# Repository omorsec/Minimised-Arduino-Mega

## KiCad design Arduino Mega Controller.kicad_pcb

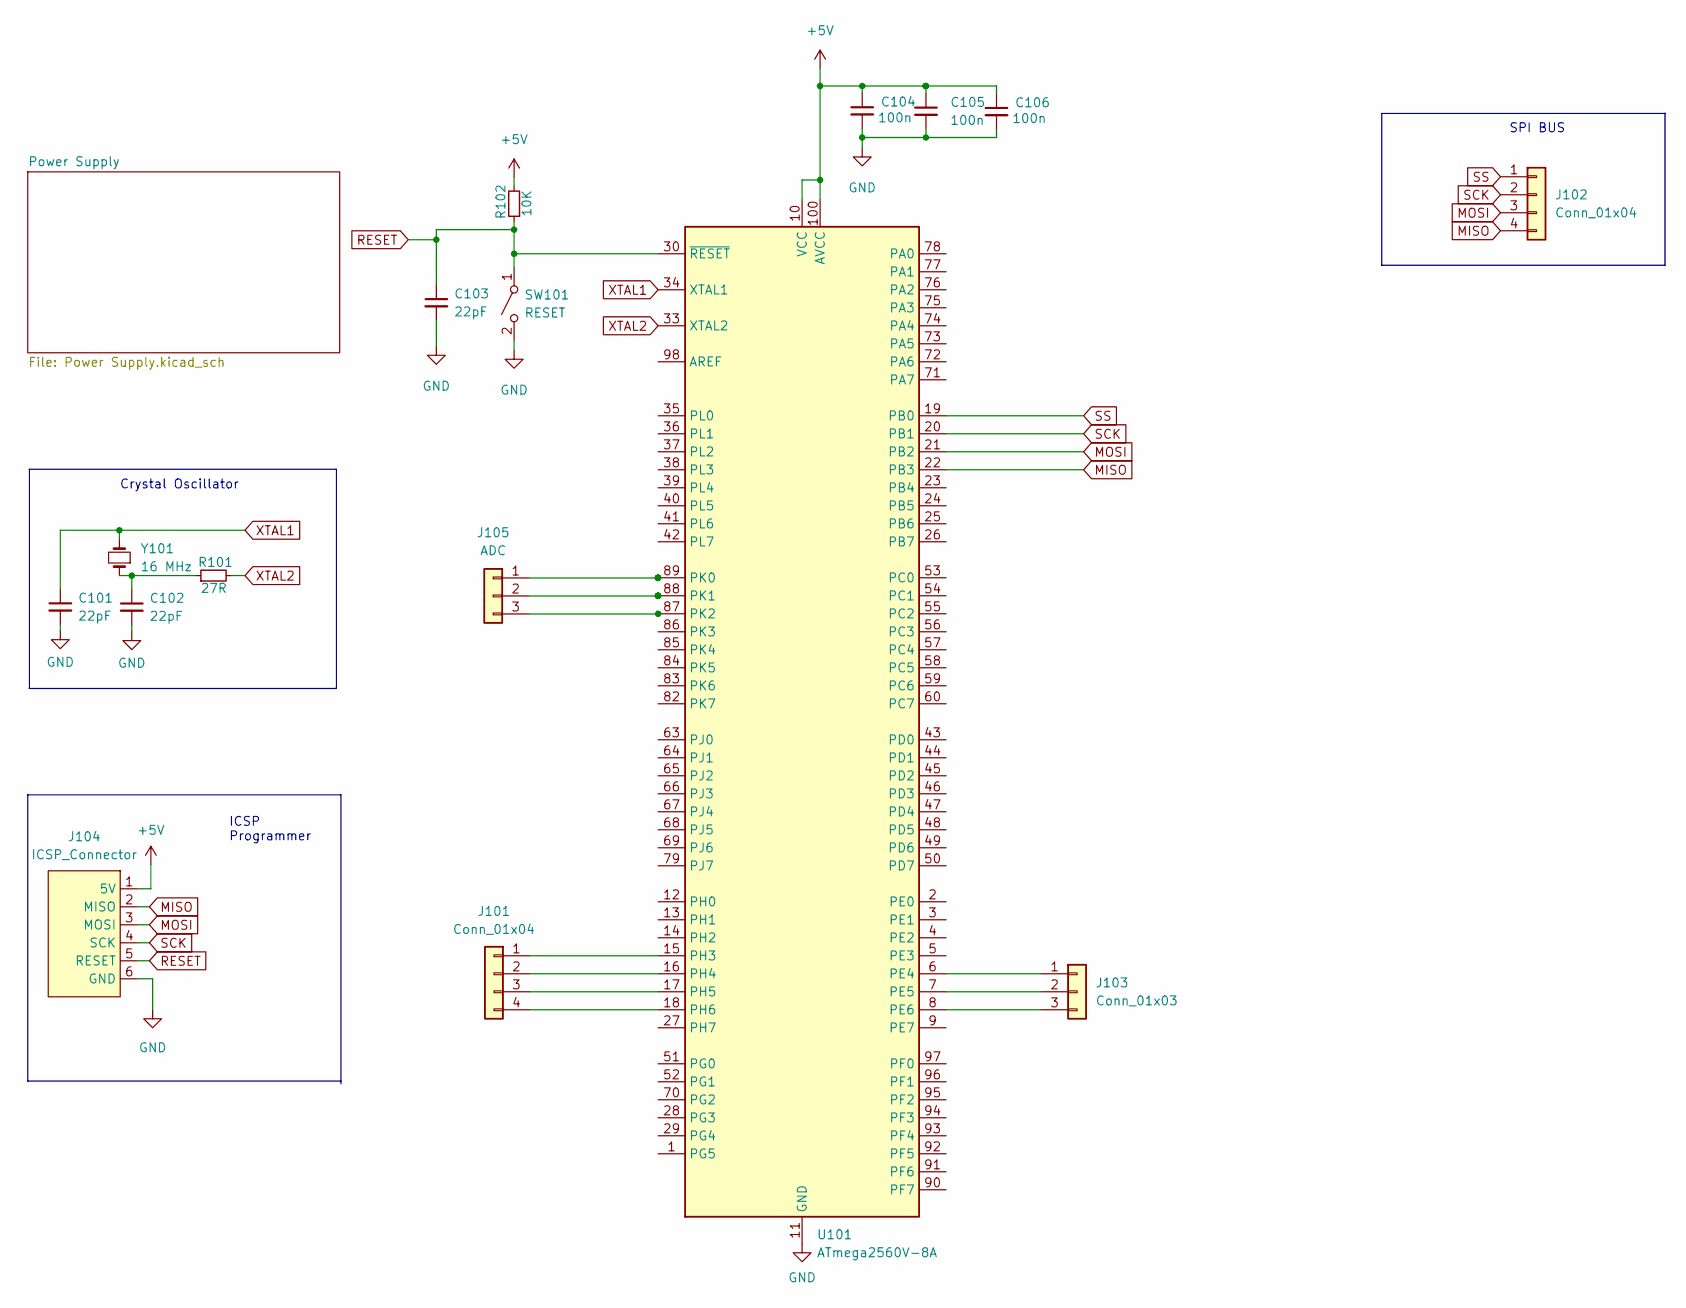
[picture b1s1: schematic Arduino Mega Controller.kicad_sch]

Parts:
C101, C102, C103: 22pF; C_0402_1005Metric; Manufacturer Part No. 04023A220KAT2A
C104, C105, C106: 100n; C_0402_1005Metric; Manufacturer Part No. C0402C104K4PAC7867
J101, J102: Conn_01x04; SIP-4_1mm Hole
J103: Conn_01x03; SIP-3_1mm Hole
J104: ICSP_Connector; SIP-6_1mm_2.54mm
J105: ADC; SIP-3_1mm Hole
R101: 27R; R_0402_1005Metric; Manufacturer Part No. CRGCQ0402F27R
R102: 10K; R_0402_1005Metric; Manufacturer Part No. RNCF0402DTE10K0
SW101: RESET; SW_SPST_PTS645; Manufacturer Part No. PTS645SL50SMTR92 LFS
U101: ATmega2560V-8A; TQFP-100_14x14mm_P0.5mm; Manufacturer Part No. ATMEGA2560-16AU
Y101: 16 MHz; XTAL_ECS-160-S-5PX-TR; Manufacturer Part No. 16M20P2/49SMT

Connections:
+5V: C104.1, C105.1, C106.1, J104.1 (5V), R102.2, U101.10 (VCC), U101.31 (VCC), U101.61 (VCC), U101.80 (VCC), U101.100 (AVCC); also elsewhere on the board
GND: C101.2, C102.2, C103.2, C104.2, C105.2, C106.2, J104.6 (GND), SW101.2 (B), U101.11 (GND), U101.32 (GND), U101.62 (GND), U101.81 (GND), U101.99 (GND); also elsewhere on the board
MISO: J102.4, J104.2 (MISO), U101.22 (PB3)
MOSI: J102.3, J104.3 (MOSI), U101.21 (PB2)
unnamed: C102.1, R101.1, Y101.1
unnamed: J101.1, U101.15 (PH3)
unnamed: J101.2, U101.16 (PH4)
unnamed: J101.3, U101.17 (PH5)
unnamed: J101.4, U101.18 (PH6)
unnamed: J103.1, U101.6 (PE4)
unnamed: J103.2, U101.7 (PE5)
unnamed: J103.3, U101.8 (PE6)
unnamed: J105.1, U101.89 (PK0)
unnamed: J105.2, U101.88 (PK1)
unnamed: J105.3, U101.87 (PK2)
RESET: C103.1, J104.5 (RESET), R102.1, SW101.1 (A), U101.30 (~RESET)
SCK: J102.2, J104.4 (SCK), U101.20 (PB1)
SS: J102.1, U101.19 (PB0)
XTAL1: C101.1, U101.34 (XTAL1), Y101.2
XTAL2: R101.2, U101.33 (XTAL2)

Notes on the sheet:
Crystal Oscillator
SPI BUS
ICSP Programmer

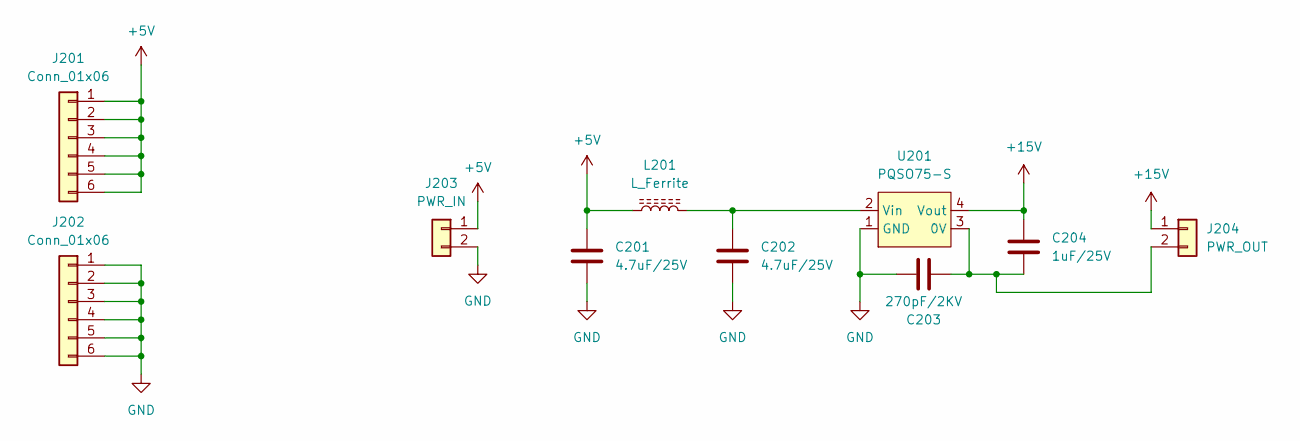
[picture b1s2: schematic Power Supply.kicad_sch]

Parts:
C201, C202: 4.7uF/25V; C_0603_1608Metric; Manufacturer Part No. 06033D475KAT2A
C203: 270pF/2KV; C_1206_3216Metric; Manufacturer Part No. C1206C271MGRAC7800
C204: 1uF/25V; C_0402_1005Metric; Manufacturer Part No. 04023D105KAT2A
J201, J202: Conn_01x06; SIP-6_1mm_2.54mm
J203: PWR_IN; SIP-2_1mm_2.54mm
J204: PWR_OUT; SIP-2_1mm_2.54mm
L201: L_Ferrite; IND_1919(4848); Manufacturer Part No. 744042006
U201: PQSO75-S; SIP-4; Manufacturer Part No. PQSO75-S

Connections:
+5V: C201.1, J201.1, J201.2, J201.3, J201.4, J201.5, J201.6, J203.1, L201.1; also elsewhere on the board
+15V: C204.1, J204.1, U201.4 (Vout)
GND: C201.2, C202.2, C203.1, J202.1, J202.2, J202.3, J202.4, J202.5, J202.6, J203.2, U201.1 (GND); also elsewhere on the board
unnamed: C202.1, L201.2, U201.2 (Vin)
unnamed: C203.2, C204.2, J204.2, U201.3 (0V)

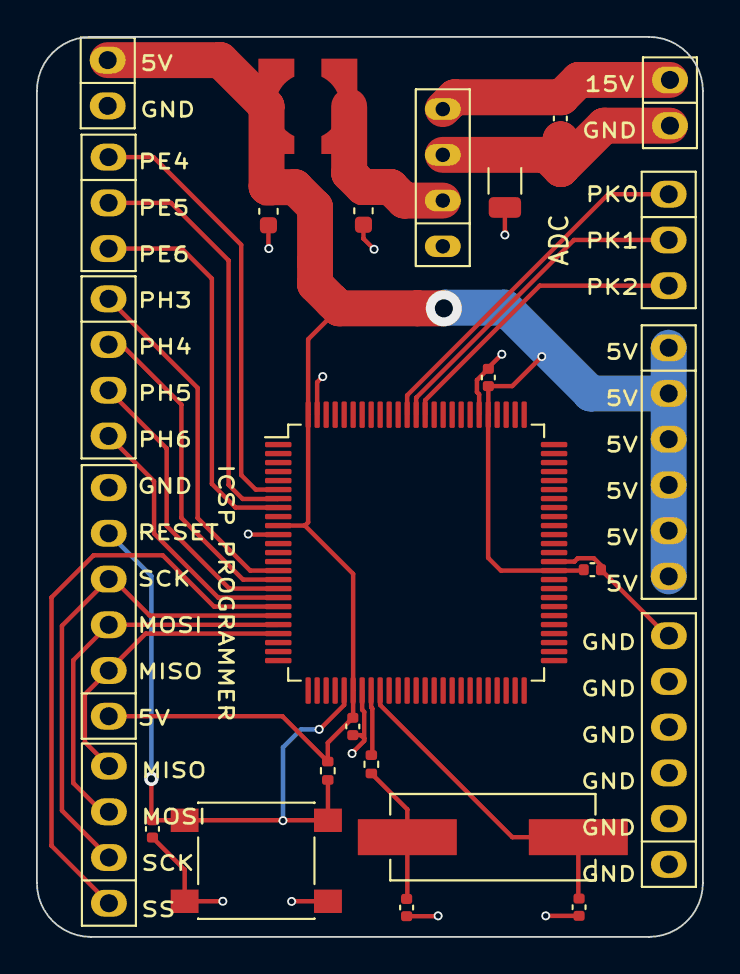
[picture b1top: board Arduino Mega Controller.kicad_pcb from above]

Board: 2 copper layers, 37.0 x 50.0 mm, 26 parts (0 on the bottom side), 23 nets.

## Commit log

2023-01-13 Final Update
